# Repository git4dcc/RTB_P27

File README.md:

# RTB_P27

This module is a decoder test board with two Plux16 ([NEM658](https://www.morop.eu/downloads/nem/de/nem658_d.pdf)) sockets and is part of my growing collection of tools for my DCC based digital model train. It has two independent Plux16 sockets, each with an optional SUSI3 connector. The DCC signal is fed in and out at both ends to enable easy daisy chaining of multiple PCBs. A motor or resistor can be connected externally to enable service mode programming with DCC.

<details>
<summary>See also</summary>

- [RTB_D22](/../../../../git4dcc/RTB_D22) (DCC Decoder)
- [RTB_P21](/../../../../git4dcc/RTB_P21)
- [RTB_P24](/../../../../git4dcc/RTB_P24)

</details>

<details>
<summary>User Guides</summary>

- User Guide - DE
- User Guide - EN

</details>

# Hardware
My PCB layout uses SMD footprints with mainly 0603 parts. Reflow soldering is my recommendation, but with some experience handsoldering is also possible.

## PCB
- 2-layer PCB, FR4, 1.6mm
- Socket: 2x Plux16 (NEM658)

## Kicad
[Schematic](doc/P27_schematic.pdf) | [Layout](doc/P27_layout.pdf) | [Gerber](gerber)

<details>
<summary>Dependency</summary>
<br>

:yellow_circle: Requires my Kicad project library [RTB_SamacSys](/../../../../git4dcc/RTB_SamacSys) in the same directory tree.

</details>

# Images

This project is intended for hobby use only and is distributed in accordance with the Apache License 2.0 agreement.

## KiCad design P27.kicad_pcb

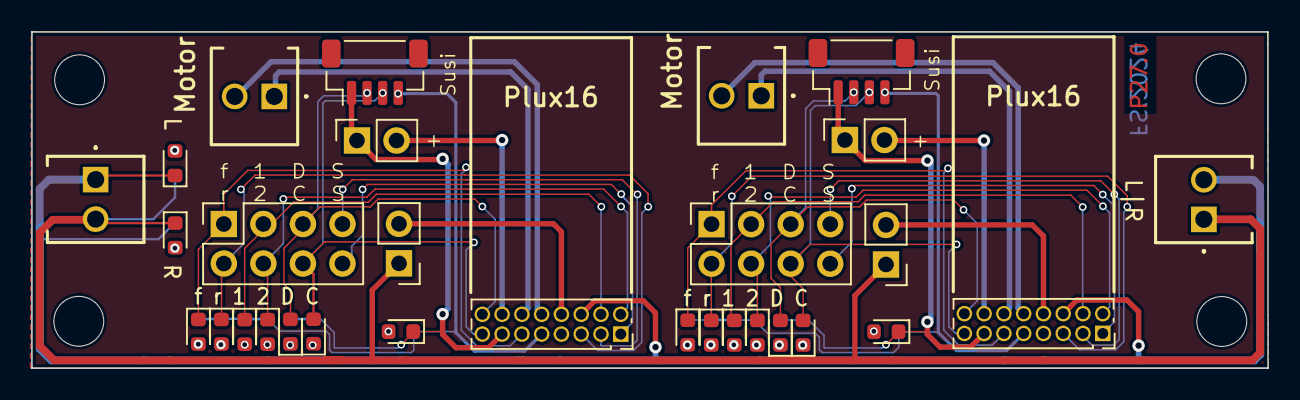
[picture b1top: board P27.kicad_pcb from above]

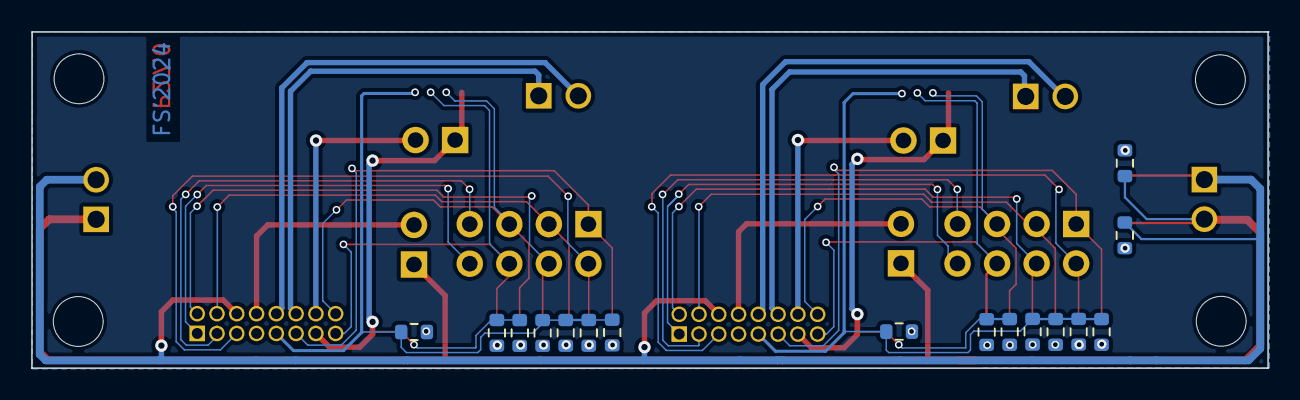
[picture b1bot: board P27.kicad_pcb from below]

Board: 2 copper layers, 79.4 x 21.6 mm, 50 parts (16 on the bottom side), 46 nets.

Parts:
D1, D2, D3, D4, D5, D6, D7, D8, D9, D10, D11, D12, D13, D16, D17, D20: LED_Small_ALT; LED_0603_1608Metric
H1, H2, H3, H4: MountingHole; MountingHole_3.2mm_M3_DIN965
J1, J6: Conn_01x08; PinSocket_2x04_P2.54mm_Vertical
J2, J4: Conn_02x08_Counter_Clockwise; PinSocket_2x08_P1.27mm_Vertical
J3, J7: Conn_01x03_Male; PinSocket_1x02_P2.54mm_Vertical
J5, J8: Conn_01x02; PinHeader_1x02_P2.54mm_Vertical
J9, J10: DCC; 1725656
J11, J12: Conn_01x03_Male; 1725656
J13, J14: Conn_01x04; JST_SH_BM04B-SRSS-TB_1x04-1MP_P1.00mm_Vertical
R1, R2, R3, R4, R5, R6, R7, R8, R9, R10, R19, R20: 10k; R_0603_1608Metric
R11, R12, R15, R16: 2.2k; R_0603_1608Metric

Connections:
Aux1.a: D6.1, J4.4, J6.3
Aux1.b: D4.1, J1.3, J2.4
Aux2.a: D7.1, J4.2, J6.4
Aux2.b: D5.1, J1.4, J2.2
Cap+.a: J4.14, J7.2
Cap+.b: J2.14, J3.2
Clk.a: D17.2, J4.15, J6.6, J14.3
Clk.b: D13.2, J1.6, J2.15, J13.3
Dat.a: D16.2, J4.16, J6.5, J14.2
Dat.b: D12.2, J1.5, J2.16, J13.2
F0_f.a: D9.1, J4.11, J6.1
F0_f.b: D3.1, J1.1, J2.11
F0_r.a: D8.1, J4.5, J6.2
F0_r.b: D2.1, J1.2, J2.5
GND.a: D20.1, J4.13, J7.1, J14.1, R15.2, R16.2
GND.b: D1.1, J2.13, J3.1, J13.1, R11.2, R12.2
LSA.a: J4.3, J6.7
LSA.b: J1.7, J2.3
LSB.a: J4.1, J6.8
LSB.b: J1.8, J2.1
Mot+.a: J4.12, J12.1
Mot+.b: J2.12, J11.1
Mot-.a: J4.10, J12.2
Mot-.b: J2.10, J11.2
unnamed: D1.2, R19.1
unnamed: D2.2, R1.1
unnamed: D3.2, R2.1
unnamed: D4.2, R3.1
unnamed: D5.2, R4.1
unnamed: D6.2, R5.1
unnamed: D7.2, R6.1
unnamed: D8.2, R7.1
unnamed: D9.2, R8.1
unnamed: D10.1, J5.1, J8.1, J9.1, J10.2, R10.2
unnamed: D10.2, R9.1
unnamed: D11.1, J2.6, J4.6, J9.2, J10.1, R9.2
unnamed: D11.2, R10.1
unnamed: D12.1, R11.1
unnamed: D13.1, R12.1
unnamed: D16.1, R15.1
unnamed: D17.1, R16.1
unnamed: D20.2, R20.1
unnamed: J2.8, J8.2
unnamed: J4.8, J5.2
U+.a: J4.9, J14.4, R5.2, R6.2, R7.2, R8.2, R20.2
U+.b: J2.9, J13.4, R1.2, R2.2, R3.2, R4.2, R19.2

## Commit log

2024-12-08 initial
2026-02-20 Update links in README.md to relative paths
2026-02-20 git mirror test

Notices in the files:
P27.kicad_pcb:
Licensed under the Apache License, Version 2
